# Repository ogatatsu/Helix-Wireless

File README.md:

# Helix-Wireless

[Helix](https://github.com/MakotoKurauchi/helix)に[BL652-breakout](https://github.com/ogatatsu/BL652-breakout)
を載せてワイヤレスに改造した物。

## 仕組み
以下の図のようにマスター、スレーブ、PC間で通信する。

スイッチ１つ１つに一意なIDが振られていて、スレーブマスター間では押されたスイッチのIDを通信でやり取りする、
マスター側では受け取ったスレーブ側で押されたIDと自分側で押されたIDをキーマップからキーコードに変換してPCに送る。
キーマップはマスター側で持っているのでキー配列を変更する時はマスター側のプログラムを変更が必要となる。

## ビルド方法
- BL652-breakoutには予めFeather nRF52のブートローダーを書き込んでおく。

  参考URL
  
  https://learn.adafruit.com/bluefruit-nrf52-feather-learning-guide/flashing-the-bootloader
  https://qiita.com/ogatatsu@github/items/37f4888c885c4e287df1

- BL652-breakoutを右側、左側共にHelix PCBの白枠線内とは逆の方に刺す。(画像の赤い方)

- ArduinoをインストールしてボードマネージャーからFeather nRF52用の物をインストールしておく。

  参考URL

  https://learn.adafruit.com/bluefruit-nrf52-feather-learning-guide/arduino-bsp-setup

- ArduinoのライブラリマネージャからBounce2ライブラリをインストールする。
- Arduino IDEで.inoファイルを開いて右側のボードにはSlave用のファームウェア、左側にはMaster用のファームウェアを書き込む。

## キーカスタマイズ
キーのカスタマイズはマスター側のソースの`keymap.cpp`ファイルを書き換えることでできる。

通常の入力時のカスタマイズは`keymap[]`配列を変更する。

```c++
static Key keymap[] = {
    {1, L(NK(_GRAVE), CK(_SHIFT, _GRAVE), NK(_GRAVE))},
    {2, L(NK(_1), CK(_SHIFT, _1), NK(_1))},
    {3, L(NK(_2), CK(_SHIFT, _2), NK(_2))},
    {4, L(NK(_3), CK(_SHIFT, _3), NK(_3))},
    {5, L(NK(_4), CK(_SHIFT, _4), NK(_4))},
    ...
```

左側の数字は仕組みで説明した一意なID、右側の関数呼び出しはファームウェア内でコマンドと呼ばれる物でこれの組み合わせを変更することでIDを割り当てられたスイッチを押したときの挙動を変更できる。

どのスイッチが何番のIDに割り当てられているかは以下となる。

```
/* ID
   * ,-----------------------------------------.             ,-----------------------------------------.
   * |   1  |   2  |   3  |   4  |   5  |   6  |             |   7  |   8  |   9  |  10  |  11  |  12  |
   * |------+------+------+------+------+------|             |------+------+------+------+------+------|
   * |  13  |  14  |  15  |  16  |  17  |  18  |             |  19  |  20  |  21  |  22  |  23  |  24  |
   * |------+------+------+------+------+------|             |------+------+------+------+------+------|
   * |  25  |  26  |  27  |  28  |  29  |  30  |             |  31  |  32  |  33  |  34  |  35  |  36  |
   * |------+------+------+------+------+------+------+------+------+------+------+------+------+------|
   * |  37  |  38  |  39  |  40  |  41  |  42  |  43  |  44  |  45  |  46  |  47  |  48  |  49  |  50  |
   * |------+------+------+------+------+------+------+------+------+------+------+------+------+------|
   * |  51  |  52  |  53  |  54  |  55  |  56  |  57  |  58  |  59  |  60  |  61  |  62  |  63  |  64  |
   * `-------------------------------------------------------------------------------------------------'
   */
```

## コマンド一覧
### NOPコマンド
```
Command *NOP
```
何もしないコマンド、以下の例では`SW1`を押しても何も起こらない。
```c++
static Key keymap[] = {
    {1, NOP},
};
```

### NKコマンド
```c++
Command *NK(uint8_t keycode)
```
通常キー用のコマンド、以下の例では`SW1`は`A`,`SW2`は`B`,`SW3`は`C`のキーコードを送出する。
(`keycode.h`ファイルにキーコードに対して`_A`などの名前が割り当てられているのでそちらも参照のこと。)
```c++
static Key keymap[] = {
    {1, NK(_A)},
    {2, NK(_B)},
    {3, NK(_C)},
};
```

### MOコマンド
```c++
Command *MO(Modifier modifier)
```
修飾キー用のコマンド、以下の例では`SW1`は`SHIFT`のキーコードを、`SW2`は`CTRL`と`SHIFT`のキーコードを同時に送出する。
修飾キーは`|`演算子で同時押しの組み合わせを表現できる。
```c++
static Key keymap[] = {
    {1, MO(_SHIFT)},
    {2, MO(_CTRL | _SHIFT)},
};
```

### CKコマンド
```c++
Command *CK(Modifier modifier, uint8_t keycode)
```
コンビネーションキー用のコマンド、修飾キーと通常キーの同時押しを表現できる。以下の例は`SW1`は`CTRL+C`、`SW2`は`CTRL+ALT+DELETE`のキーコードを送出する。
```c++
static Key keymap[] = {
    {1, CK(_CTRL, _C)},
    {2, CK(_CTRL | _ALT, _DELETE)},
};
```

### MTコマンド
```c++
Command *MT(Modifier modifier, uint8_t keycode)
```
スイッチを押した後リリースせずにに別のスイッチを押したときは第1引数の修飾キー、スイッチ単体でタップすると第2引数の通常キーとして機能するコマンド、以下の例で`SW1`を押した後離さずに`SW2`を押すと`SHIFT`キー（結果として`SHIFT+A`）、`SW1`を押して何もせずにそのまま離すと`SPACE`キーのキーコードが送出される。
```c++
static Key keymap[] = {
    {1, MT(_SHIFT, _SPACE)},
    {2, NK(_A)},
};
```

### OSMコマンド
```c++
Command *OSM(Modifier modifier)
```
スイッチを押して離すと次にスイッチを押した時に送出されるキーコードと同時に引数の修飾キーも送出される、スイッチを押して離さずに別のスイッチを押した場合は通常の修飾キーコマンドの様に動作する。下の例では`SW1`を押して離した後に`SW2`を押すと`SHIFT+A`のキーコードが送出される。
```c++
static Key keymap[] = {
    {1, OSM(_SHIFT)},
    {2, NK(_A)},
};
```

### Lコマンド
```c++
Command *L(Command *first, Commands... rest)
```
レイヤー分けをするコマンド、現在のレイヤーの状態によって動作させるコマンドを変更する。以下の例では`SW1`を押すとレイヤー2がONの時は`C`、2がOFFで1がONの時は`B`、2と1がOFFの時は`A`のキーコードを送出する、0レイヤーはデフォルトでONとなる。
```c++
static Key keymap[] = {
    //    0     , 1     , 2
    {1, L(NK(_A), NK(_B), NK(_C))},
};
```

### SLコマンド
```c++
Command *SL(uint8_t layerNumber)
```
スイッチを押してる間だけ引数の番号のレイヤーをONにする。以下の例では`SW1`単体で押すと`A`、`SW2`を押しながら`SW1`を押すと`B`、`SW3`を押しながら`SW1`を押すと`C`のキーコードを送出する。レイヤー番号の数字が高いほうのコマンドが優先されるので`SW2`と`SW3`を同時に押しながら`SW1`を押すと`SW3`のレイヤー番号の`2`が優先され`C`のキーコードが送出される。
```c++
static Key keymap[] = {
    {1, L(NK(_A), NK(_B), NK(_C))},
    {2, SL(1)},
    {3, SL(2)},
};
```

### TLコマンド
```c++
Command *TL(uint8_t layerNumber)
```
スイッチを押したら引数の番号のレイヤーをトグルする、SLコマンドと違いスイッチを離したあとでもレイヤーをONにし続ける事ができる。以下の例だと１回`SW2`を押すとレイヤー1がONになりその状態で`SW1`を押すと`B`のキーコードを送出する。もう１回`SW2`を押すとレイヤー1がONからOFFに変わりその状態で`SW1`を押すと`A`のキーコードを送出する。
```c++
static Key keymap[] = {
    {1, L(NK(_A), NK(_B))},
    {2, TL(1)},
};
```
### LTコマンド
```c++
Command *LT(uint8_t layerNumber, uint8_t keycode)
```
MTコマンドのレイヤー版。

### OSLコマンド
```c++
Command *OSL(uint8_t layerNumber)
```
OSMコマンドのレイヤー版。

続く

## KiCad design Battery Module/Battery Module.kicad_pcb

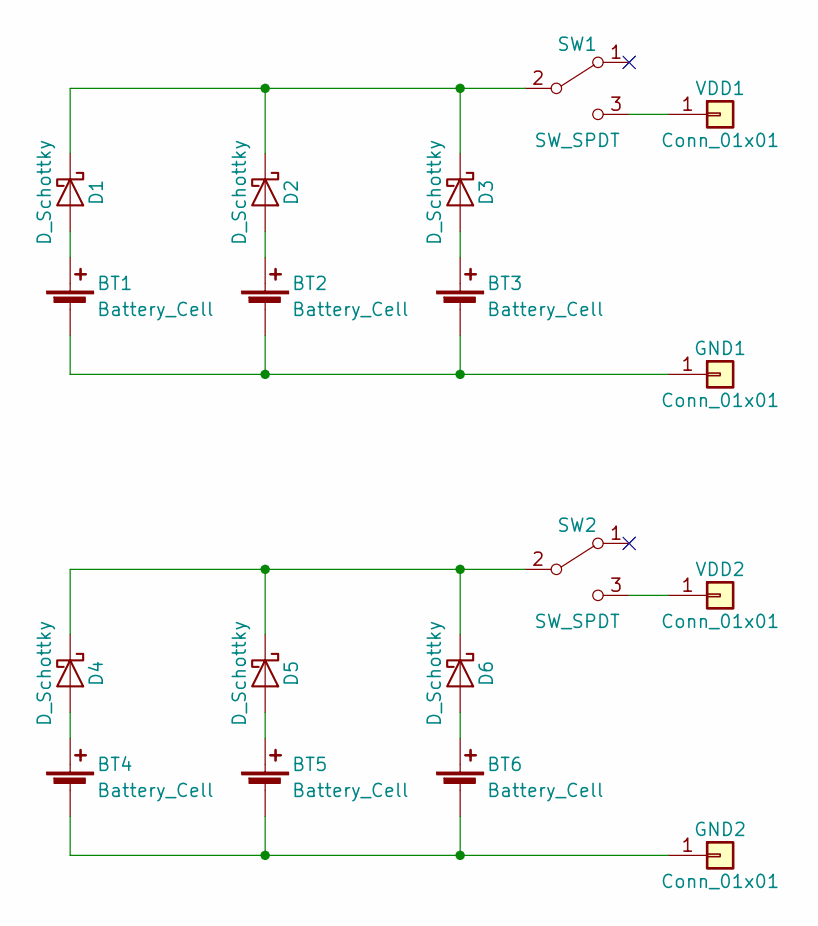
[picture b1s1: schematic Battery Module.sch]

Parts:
BT1, BT2, BT3, BT4, BT5, BT6: Battery_Cell; BHSD-2032-SM
D1, D2, D3, D4, D5, D6: D_Schottky; SS2040FL
GND1, GND2: Conn_01x01; 2060
SW1, SW2: SW_SPDT; SSSS811101
VDD1, VDD2: Conn_01x01; 2060

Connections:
unnamed: BT1.1 (+), D1.2 (A)
unnamed: BT1.2 (-), BT2.2 (-), BT3.2 (-), GND1.1
unnamed: BT2.1 (+), D2.2 (A)
unnamed: BT3.1 (+), D3.2 (A)
unnamed: BT4.1 (+), D4.2 (A)
unnamed: BT4.2 (-), BT5.2 (-), BT6.2 (-), GND2.1
unnamed: BT5.1 (+), D5.2 (A)
unnamed: BT6.1 (+), D6.2 (A)
unnamed: D1.1 (K), D2.1 (K), D3.1 (K), SW1.2 (B)
unnamed: D4.1 (K), D5.1 (K), D6.1 (K), SW2.2 (B)
unnamed: SW1.3 (C), VDD1.1
unnamed: SW2.3 (C), VDD2.1

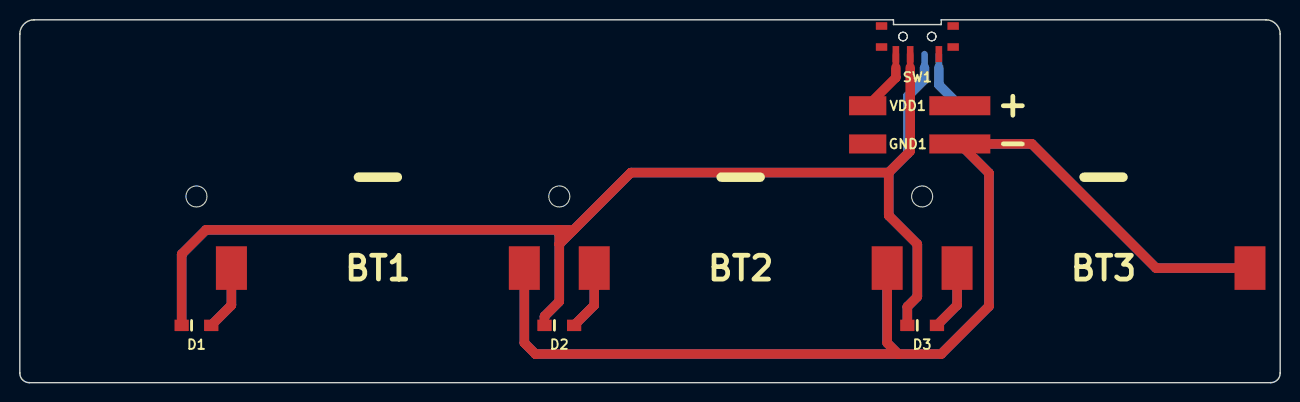
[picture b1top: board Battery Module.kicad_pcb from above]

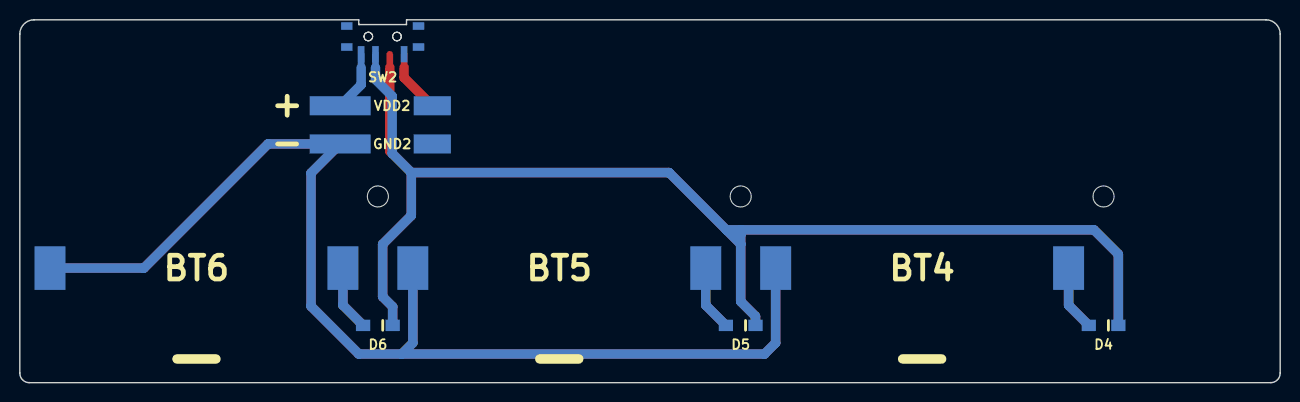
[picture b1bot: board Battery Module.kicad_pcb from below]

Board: 2 copper layers, 132.0 x 38.0 mm, 18 parts (9 on the bottom side), 12 nets.

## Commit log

2018-02-11 add image
2018-02-11 update image
2018-04-07 add battery module
2018-04-07 add battery module schematic
